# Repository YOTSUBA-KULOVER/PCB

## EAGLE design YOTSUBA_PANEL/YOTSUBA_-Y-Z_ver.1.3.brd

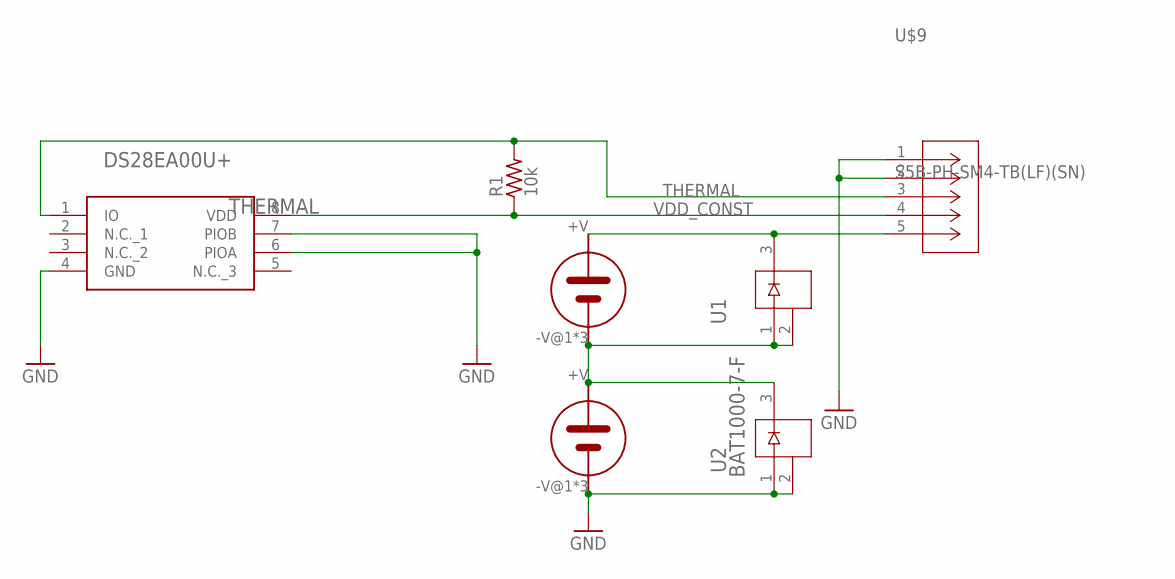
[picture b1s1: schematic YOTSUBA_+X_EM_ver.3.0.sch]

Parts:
R1: 10k; R0805
THERMAL: DS28EA00U+; SOP65P490X110-8N
U1, U2: BAT1000-7-F; SOT23_BAT_DIO
U$2, U$3: 3G30A; SOLAR_3G30A
U$9: S5B-PH-SM4-TB(LF)(SN); CONN_S5B-PH-SM4-TB_JST

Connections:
unnamed: U1.1, U1.2, U2.3, U$2.-V@1 (-V), U$2.-V@2 (-V), U$2.-V@3 (-V), U$3.+V
unnamed 1: U1.3, U$2.+V, U$9.5; also elsewhere on the board

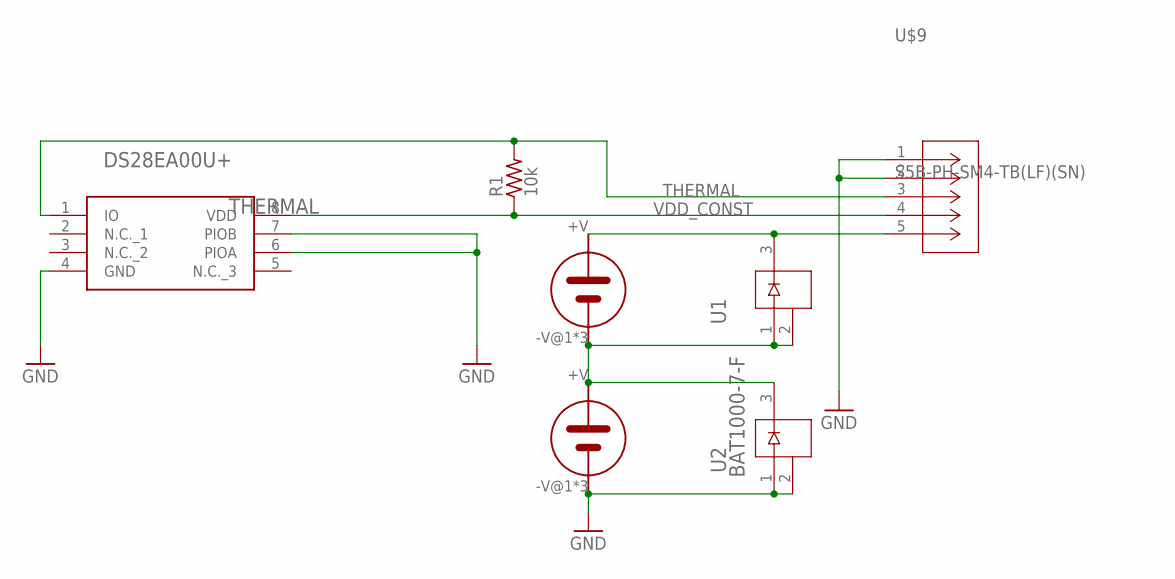
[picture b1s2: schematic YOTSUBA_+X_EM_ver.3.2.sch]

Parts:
R1: 10k; R0805
THERMAL: DS28EA00U+; SOP65P490X110-8N
U1, U2: BAT1000-7-F; SOT23_BAT_DIO
U$2, U$3: 3G30A; SOLAR_3G30A
U$9: S5B-PH-SM4-TB(LF)(SN); CONN_S5B-PH-SM4-TB_JST

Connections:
unnamed: U1.1, U1.2, U2.3, U$2.-V@1 (-V), U$2.-V@2 (-V), U$2.-V@3 (-V), U$3.+V
unnamed 1: U1.3, U$2.+V, U$9.5; also elsewhere on the board

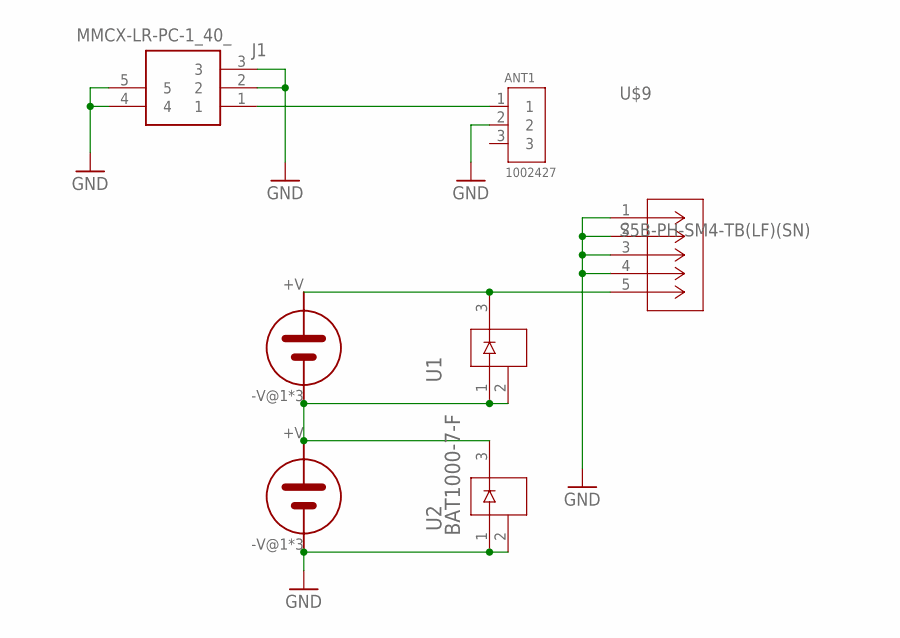
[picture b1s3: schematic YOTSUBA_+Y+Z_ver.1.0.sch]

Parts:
ANT1: 1002427; ANTENNA_1002427
J1: MMCX-LR-PC-1_40_; MMCXLRPC140
U1, U2: BAT1000-7-F; SOT23_BAT_DIO
U$2, U$3: 3G30A; SOLAR_3G30A
U$9: S5B-PH-SM4-TB(LF)(SN); CONN_S5B-PH-SM4-TB_JST

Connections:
unnamed: U1.1, U1.2, U2.3, U$2.-V@1 (-V), U$2.-V@2 (-V), U$2.-V@3 (-V), U$3.+V
unnamed 1: U1.3, U$2.+V, U$9.5; also elsewhere on the board
RF2: ANT1.1, J1.1

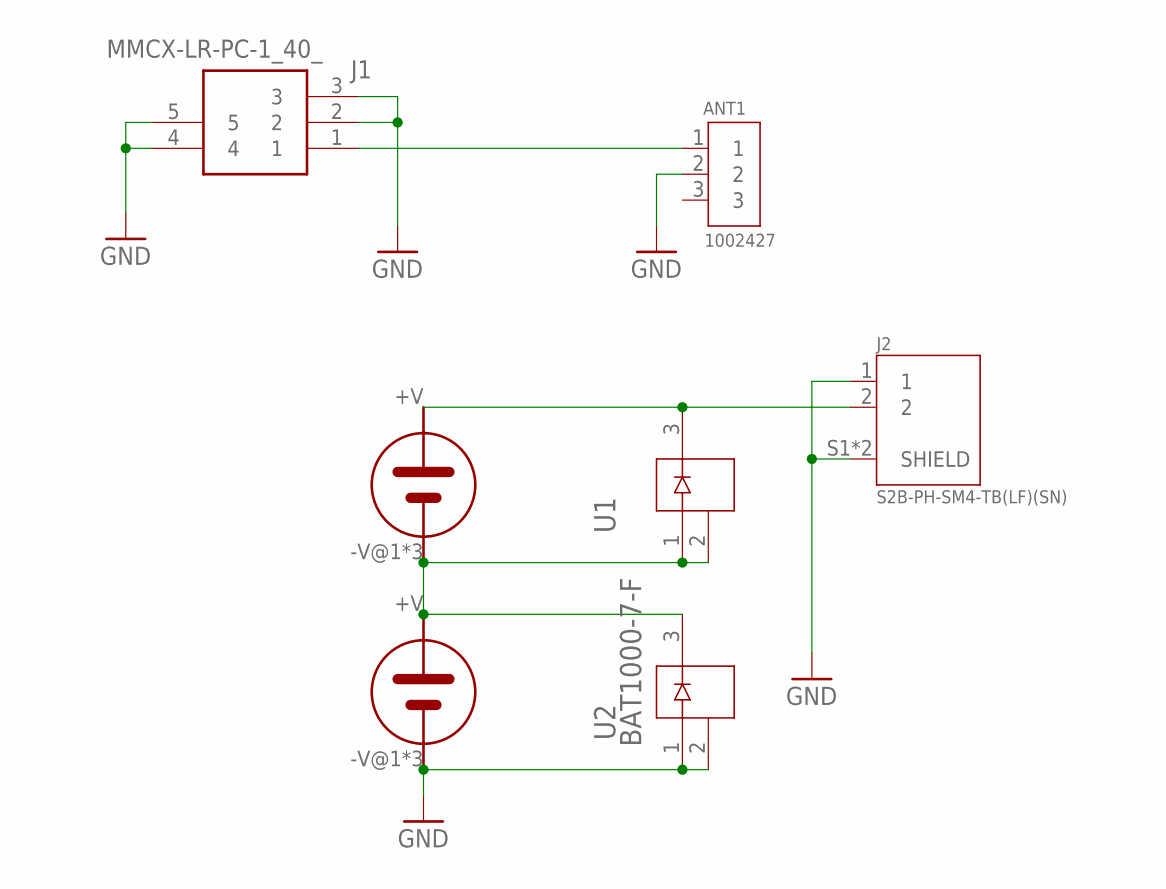
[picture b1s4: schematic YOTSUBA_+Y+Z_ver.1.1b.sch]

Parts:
ANT1: 1002427; ANTENNA_1002427
J1: MMCX-LR-PC-1_40_; MMCXLRPC140
J2: S2B-PH-SM4-TB(LF)(SN); JST_S2B-PH-SM4-TB(LF)(SN)
U1, U2: BAT1000-7-F; SOT23_BAT_DIO
U$2, U$3: 3G30A; SOLAR_3G30A

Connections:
unnamed: U1.1, U1.2, U2.3, U$2.-V@1 (-V), U$2.-V@2 (-V), U$2.-V@3 (-V), U$3.+V
unnamed 1: J2.2, U1.3, U$2.+V; also elsewhere on the board
RF2: ANT1.1, J1.1

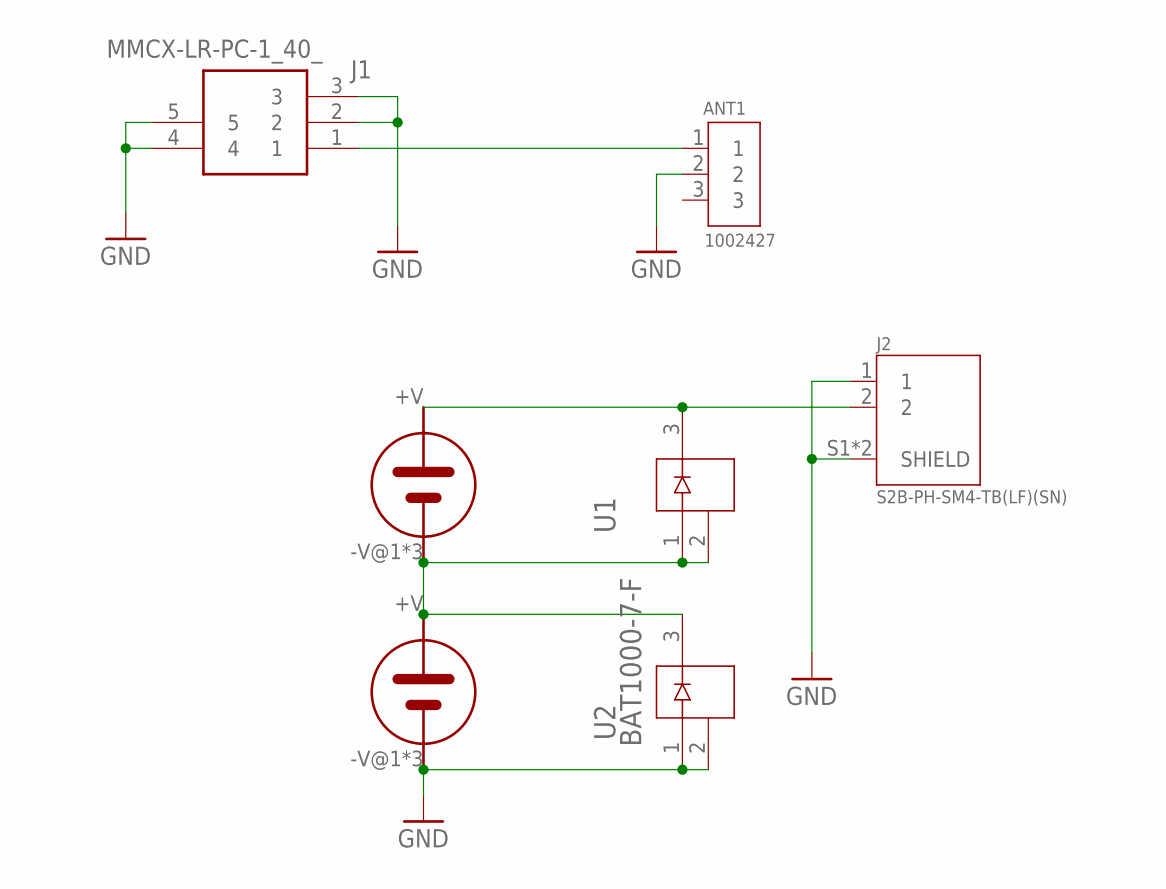
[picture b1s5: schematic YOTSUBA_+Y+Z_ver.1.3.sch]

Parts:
ANT1: 1002427; ANTENNA_1002427
J1: MMCX-LR-PC-1_40_; MMCXLRPC140
J2: S2B-PH-SM4-TB(LF)(SN); JST_S2B-PH-SM4-TB(LF)(SN)
U1, U2: BAT1000-7-F; SOT23_BAT_DIO
U$2, U$3: 3G30A; SOLAR_3G30A

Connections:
unnamed: U1.1, U1.2, U2.3, U$2.-V@1 (-V), U$2.-V@2 (-V), U$2.-V@3 (-V), U$3.+V
unnamed 1: J2.2, U1.3, U$2.+V; also elsewhere on the board
RF2: ANT1.1, J1.1

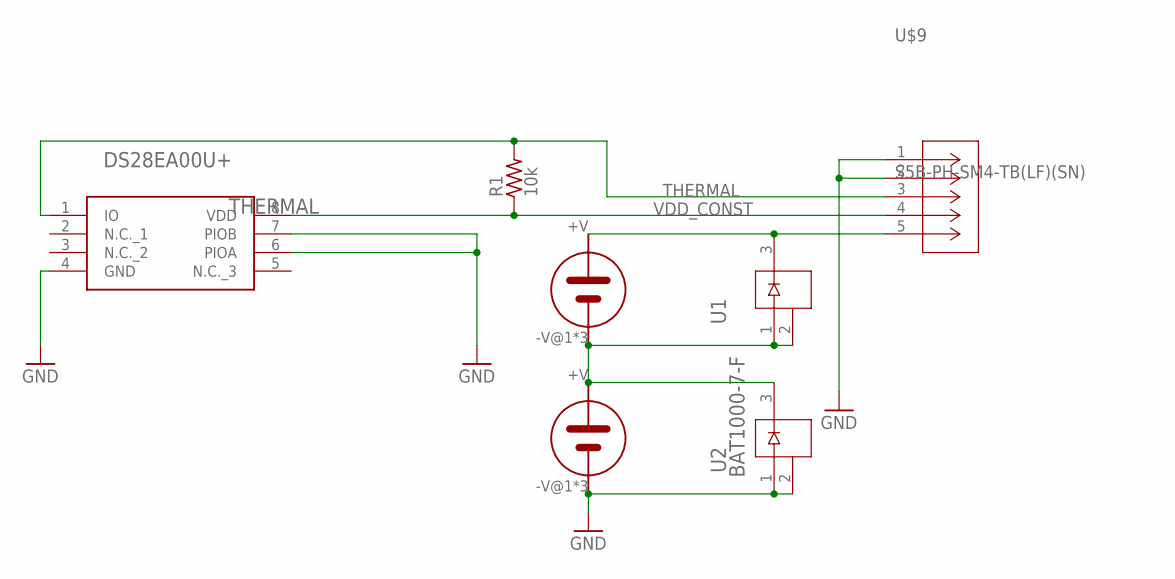
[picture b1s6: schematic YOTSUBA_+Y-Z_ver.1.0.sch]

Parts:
R1: 10k; R0805
THERMAL: DS28EA00U+; SOP65P490X110-8N
U1, U2: BAT1000-7-F; SOT23_BAT_DIO
U$2, U$3: 3G30A; SOLAR_3G30A
U$9: S5B-PH-SM4-TB(LF)(SN); CONN_S5B-PH-SM4-TB_JST

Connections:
unnamed: U1.1, U1.2, U2.3, U$2.-V@1 (-V), U$2.-V@2 (-V), U$2.-V@3 (-V), U$3.+V
unnamed 1: U1.3, U$2.+V, U$9.5; also elsewhere on the board

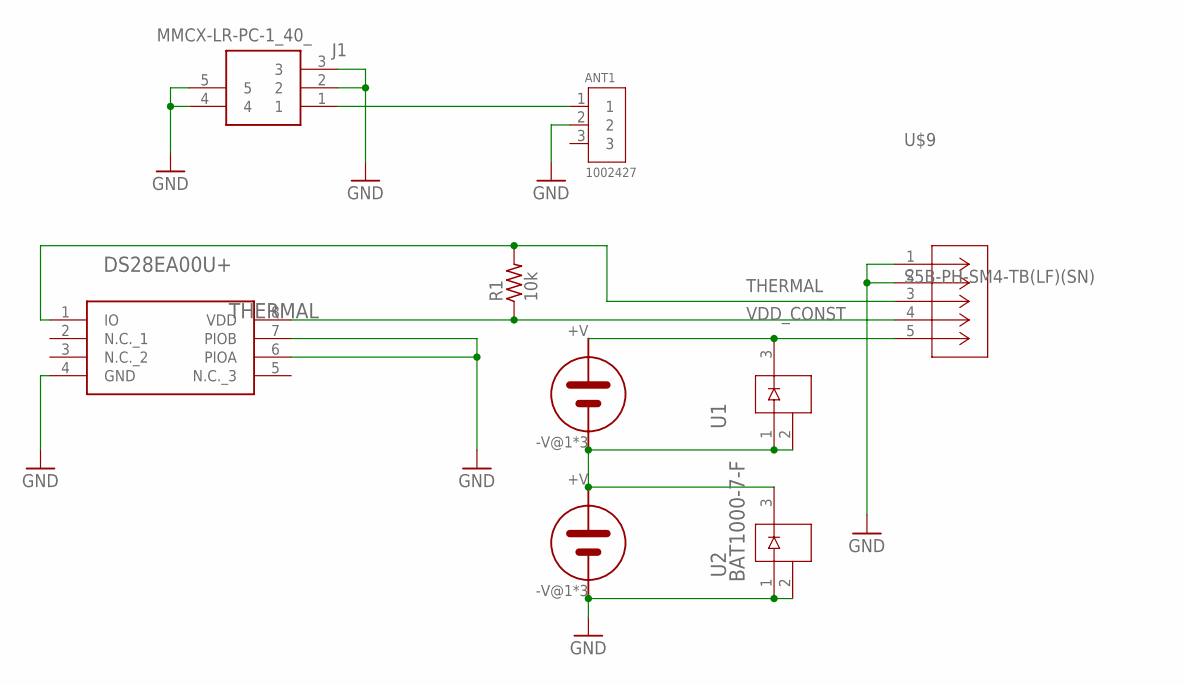
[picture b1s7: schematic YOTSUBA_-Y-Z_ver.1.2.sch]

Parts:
ANT1: 1002427; ANTENNA_1002427
J1: MMCX-LR-PC-1_40_; MMCXLRPC140
R1: 10k; R0805
THERMAL: DS28EA00U+; SOP65P490X110-8N
U1, U2: BAT1000-7-F; SOT23_BAT_DIO
U$2, U$3: 3G30A; SOLAR_3G30A
U$9: S5B-PH-SM4-TB(LF)(SN); CONN_S5B-PH-SM4-TB_JST

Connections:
unnamed: U1.1, U1.2, U2.3, U$2.-V@1 (-V), U$2.-V@2 (-V), U$2.-V@3 (-V), U$3.+V
unnamed 1: U1.3, U$2.+V, U$9.5; also elsewhere on the board
RF2: ANT1.1, J1.1

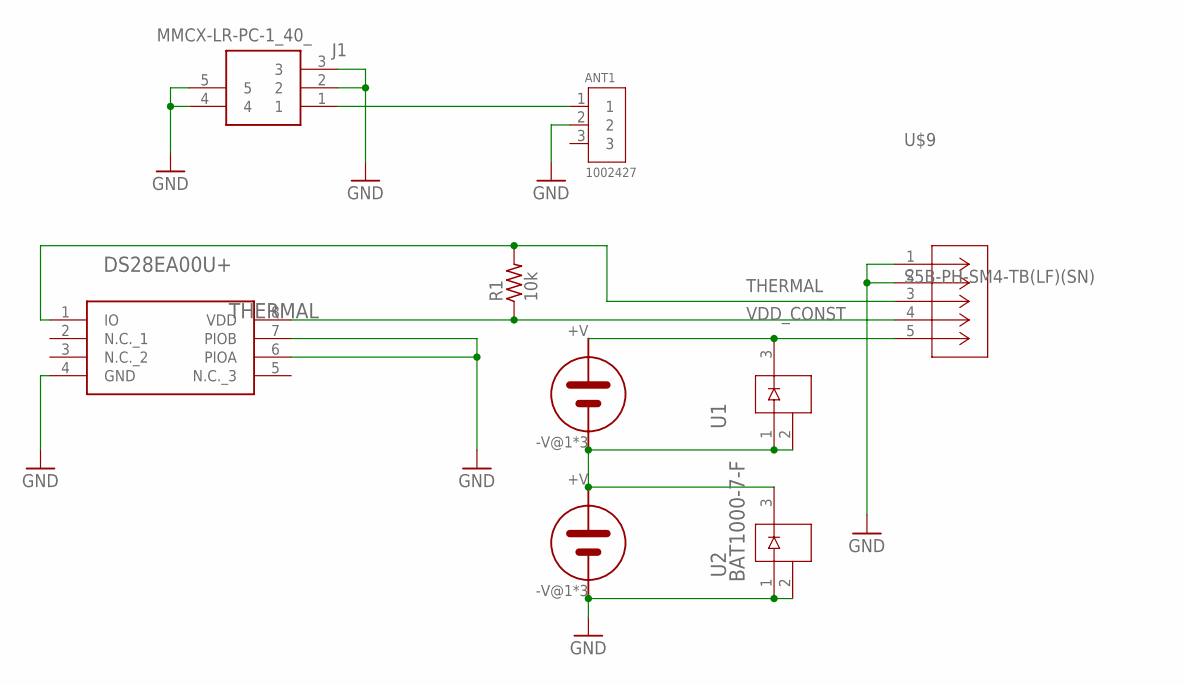
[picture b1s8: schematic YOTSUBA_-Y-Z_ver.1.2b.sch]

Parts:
ANT1: 1002427; ANTENNA_1002427
J1: MMCX-LR-PC-1_40_; MMCXLRPC140
R1: 10k; R0805
THERMAL: DS28EA00U+; SOP65P490X110-8N
U1, U2: BAT1000-7-F; SOT23_BAT_DIO
U$2, U$3: 3G30A; SOLAR_3G30A
U$9: S5B-PH-SM4-TB(LF)(SN); CONN_S5B-PH-SM4-TB_JST

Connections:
unnamed: U1.1, U1.2, U2.3, U$2.-V@1 (-V), U$2.-V@2 (-V), U$2.-V@3 (-V), U$3.+V
unnamed 1: U1.3, U$2.+V, U$9.5; also elsewhere on the board
RF2: ANT1.1, J1.1

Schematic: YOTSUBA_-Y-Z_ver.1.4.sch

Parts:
ANT1: 1002427; ANTENNA_1002427
J1: MMCX-LR-PC-1_40_; MMCXLRPC140
R1: 10k; R0805
THERMAL: DS28EA00U+; SOP65P490X110-8N
U1, U2: BAT1000-7-F; SOT23_BAT_DIO
U$2, U$3: 3G30A; SOLAR_3G30A
U$9: S5B-PH-SM4-TB(LF)(SN); CONN_S5B-PH-SM4-TB_JST

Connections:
unnamed: U1.1, U1.2, U2.3, U$2.-V@1 (-V), U$2.-V@2 (-V), U$2.-V@3 (-V), U$3.+V
unnamed 1: U1.3, U$2.+V, U$9.5; also elsewhere on the board
RF2: ANT1.1, J1.1

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
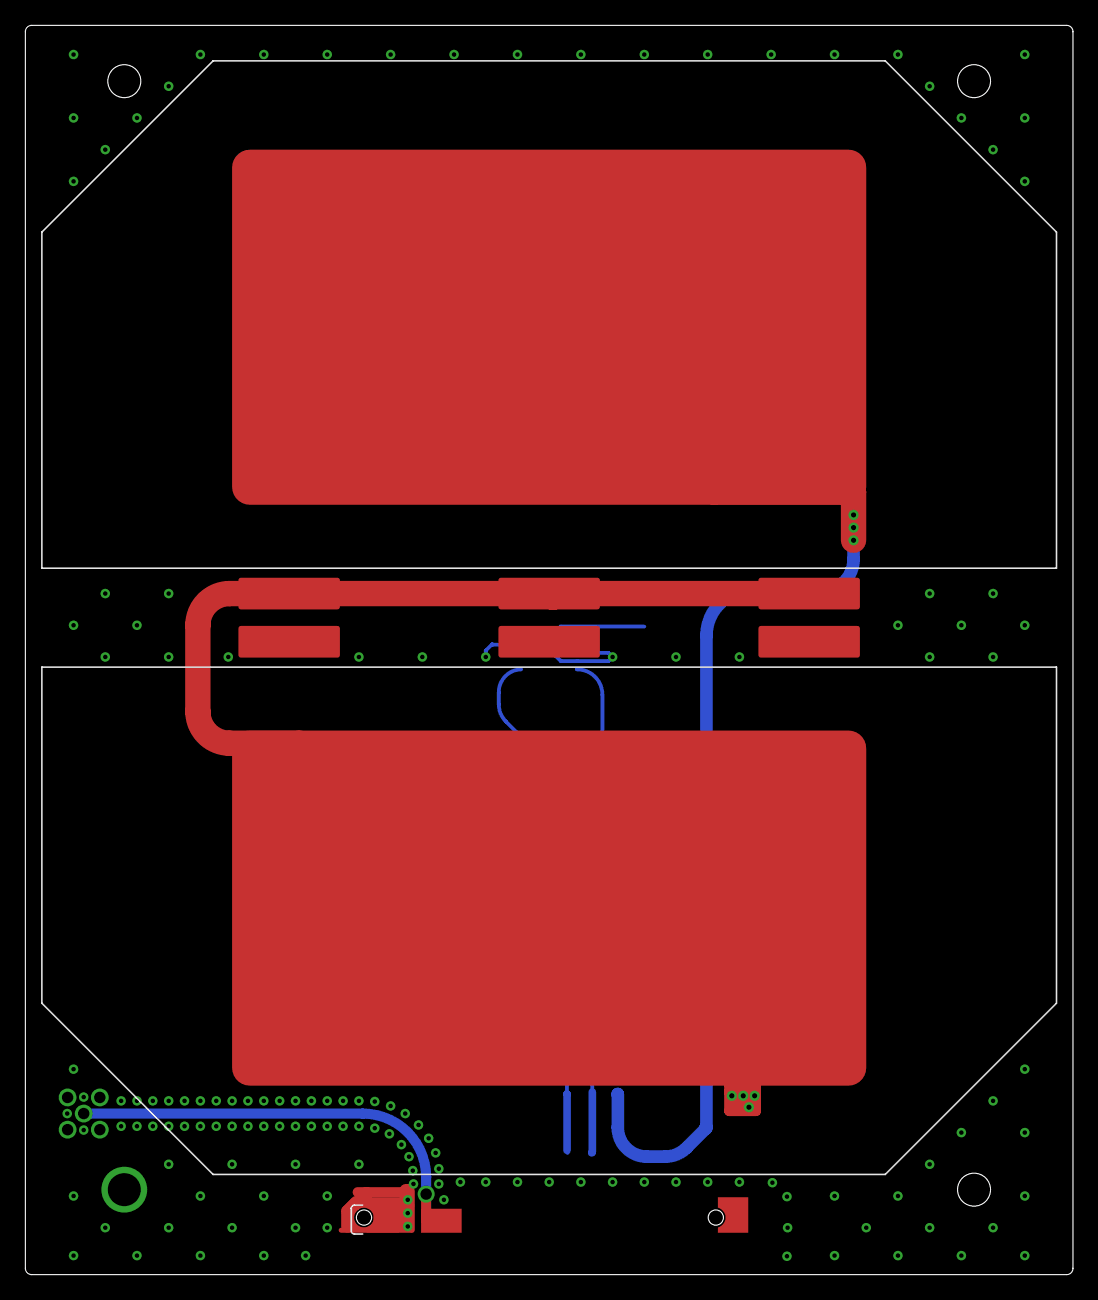
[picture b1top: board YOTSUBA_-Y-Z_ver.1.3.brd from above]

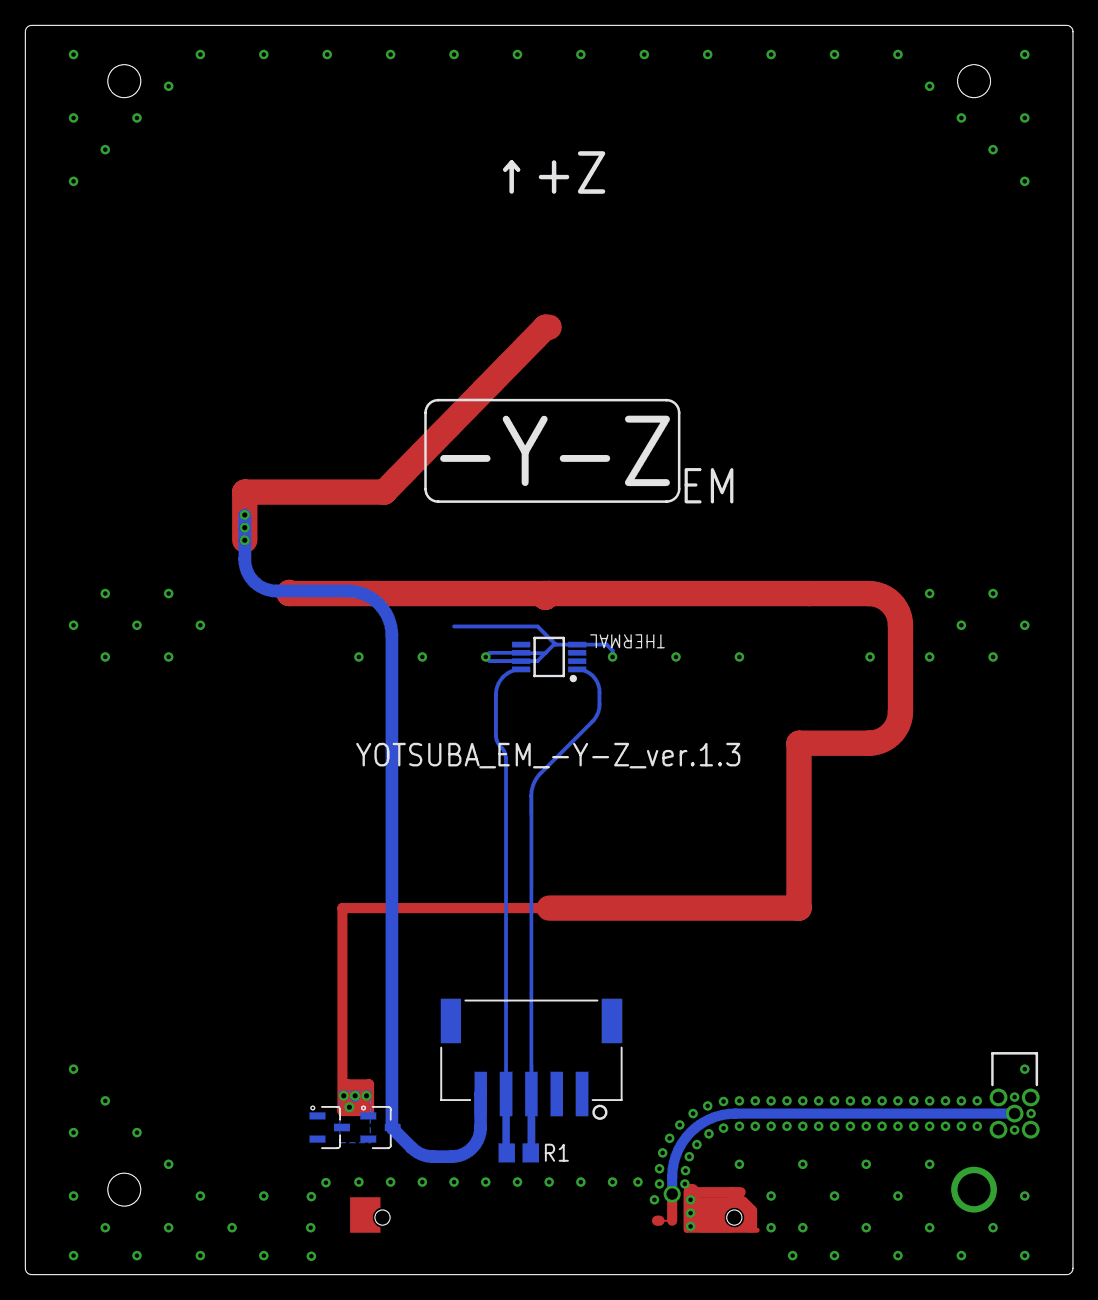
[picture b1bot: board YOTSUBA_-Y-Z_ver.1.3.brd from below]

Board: 2 copper layers, 82.6 x 98.5 mm, 9 parts (6 on the bottom side), 6 nets.

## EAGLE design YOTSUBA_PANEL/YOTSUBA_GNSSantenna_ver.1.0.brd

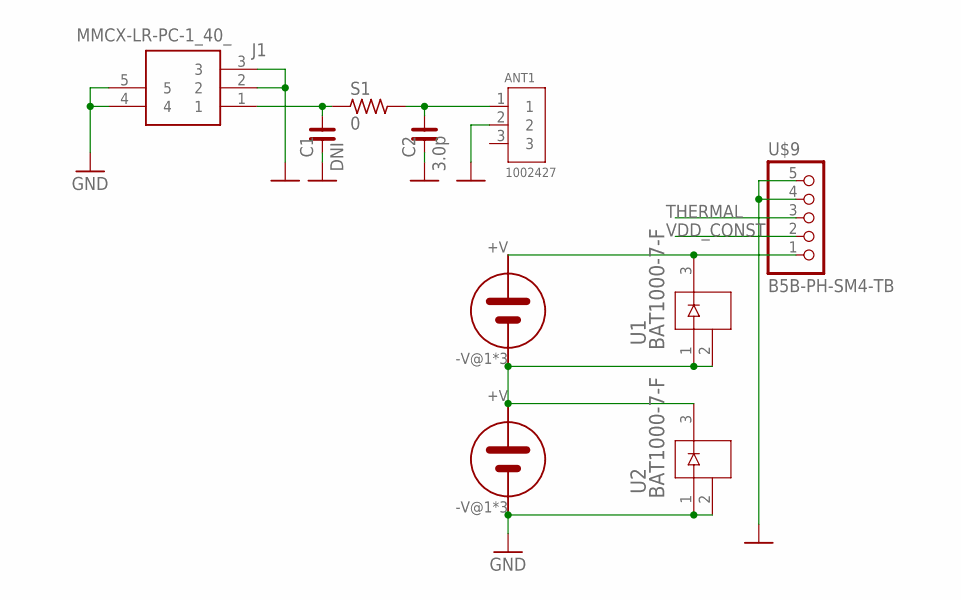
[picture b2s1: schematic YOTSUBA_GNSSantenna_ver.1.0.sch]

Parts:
ANT1: 1002427; ANTENNA_1002427
C1: DNI; C0603
C2: 3.0p; C0603
J1: MMCX-LR-PC-1_40_; MMCXLRPC140
S1: 0; R0603
U1, U2: BAT1000-7-F; SOT23_BAT_DIO
U$2, U$3: 3G30A; SOLAR_3G30A
U$9: B5B-PH-SM4-TB

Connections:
GND: ANT1.2, C1.1, C2.1, J1.2, J1.3, J1.4, J1.5, U2.1, U2.2, U$3.-V@1 (-V), U$3.-V@2 (-V), U$3.-V@3 (-V), U$9.4, U$9.5
unnamed: U1.1, U1.2, U2.3, U$2.-V@1 (-V), U$2.-V@2 (-V), U$2.-V@3 (-V), U$3.+V
unnamed: U1.3, U$2.+V, U$9.1
RF1: ANT1.1, C2.2, S1.2
RF2: C1.2, J1.1, S1.1
THERMAL: U$9.3
VDD_CONST: U$9.2

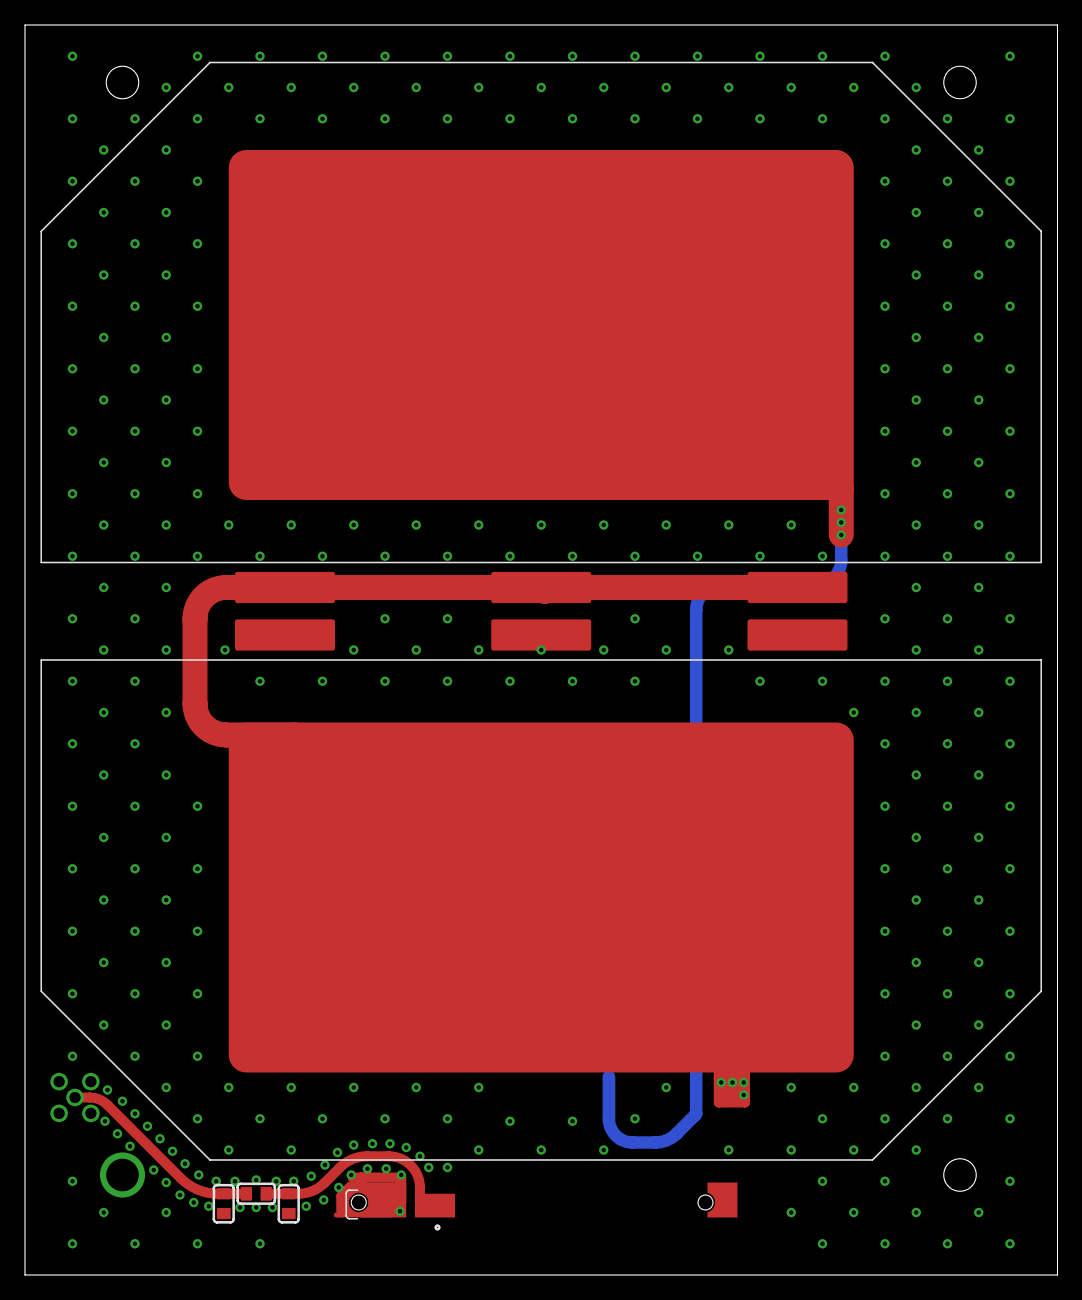
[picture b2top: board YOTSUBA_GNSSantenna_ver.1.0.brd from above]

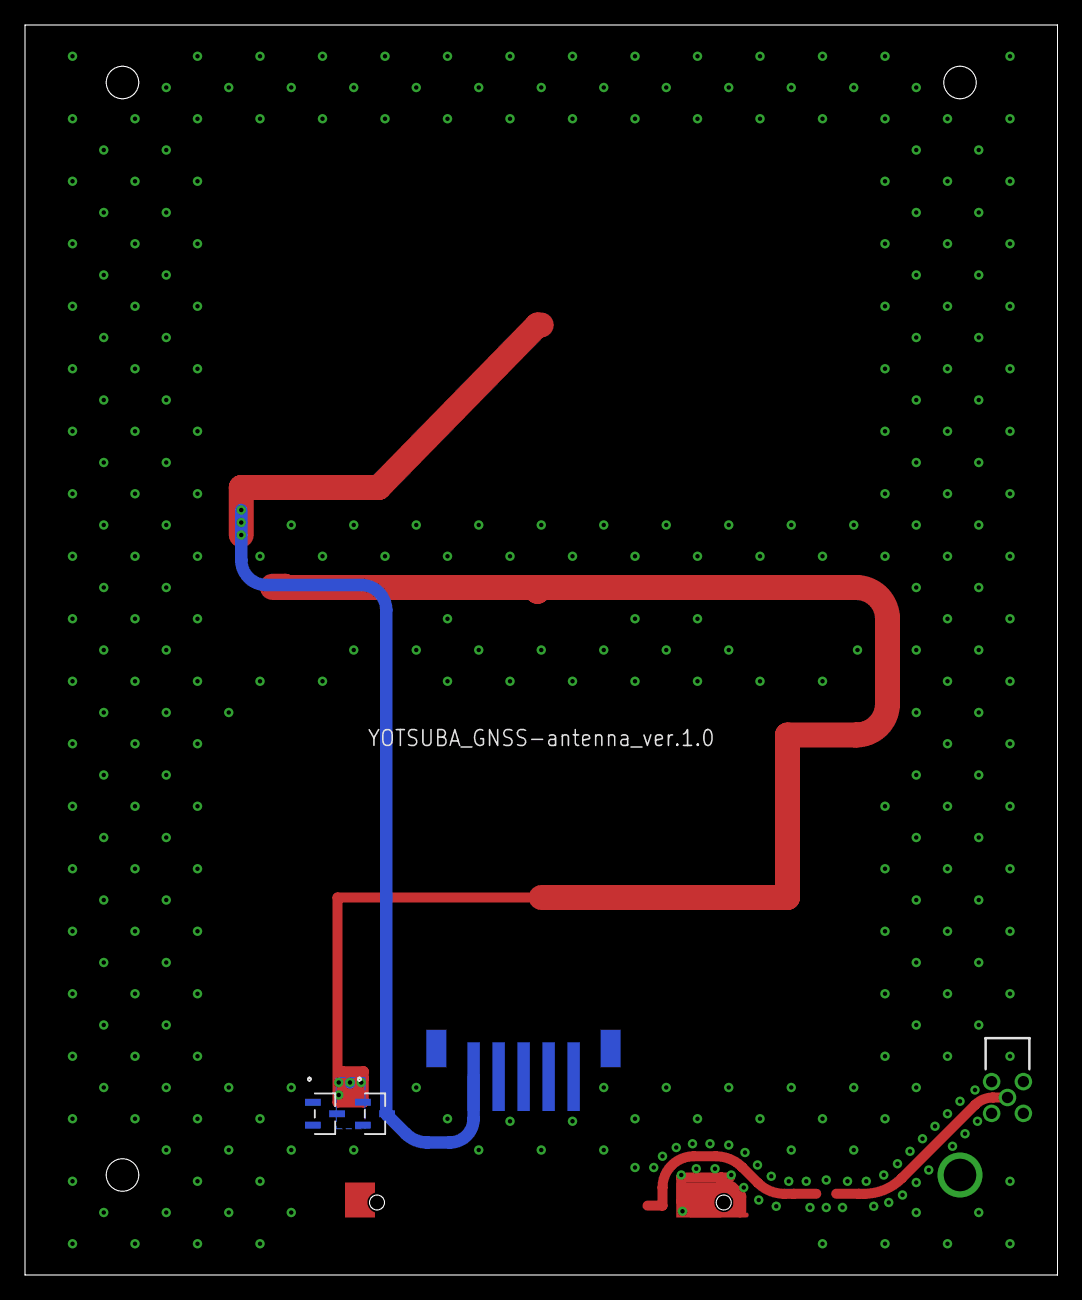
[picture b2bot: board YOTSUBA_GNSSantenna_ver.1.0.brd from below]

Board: 2 copper layers, 82.6 x 100.0 mm, 10 parts (4 on the bottom side), 5 nets.

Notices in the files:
parts and their libraries:
S5B-PH-SM4: COPYRIGHT: Copyright (C) 2023 Ultra Librarian. All rights reserved.
rc-master_custom: Copyright (C) 2007, Bob Starr
COPYRIGHT: Copyright (C) 2022 Ultra Librarian. All rights reserved.
